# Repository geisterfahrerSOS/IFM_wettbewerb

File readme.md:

# THIS IS A TEST
Beware of software BUGS/ Feautures
Changes

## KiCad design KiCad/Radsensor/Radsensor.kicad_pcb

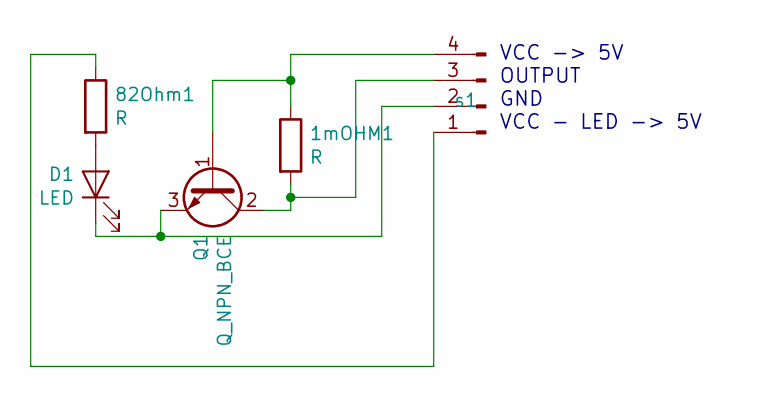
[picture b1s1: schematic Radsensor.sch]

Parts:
1mOHM1, 82Ohm1: R; R_Axial_DIN0204_L3.6mm_D1.6mm_P7.62mm_Horizontal
D1: LED; LED_D4.0mm
Q1: Q_NPN_BCE; TO-92_Inline_Wide
s1: PinHeader_1x04_P2.54mm_Horizontal

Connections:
unnamed: 1mOHM1.1, Q1.1 (B), s1.4
unnamed: 1mOHM1.2, Q1.2 (C), s1.3
unnamed: 82Ohm1.1, s1.1
unnamed: 82Ohm1.2, D1.2 (A)
unnamed: D1.1 (K), Q1.3 (E), s1.2

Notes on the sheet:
VCC -> 5V OUTPUT GND VCC - LED -> 5V

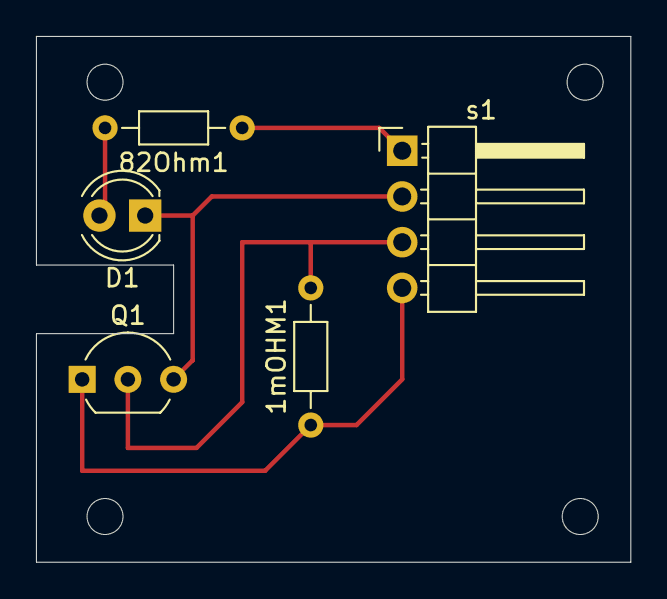
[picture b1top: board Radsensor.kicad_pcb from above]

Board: 2 copper layers, 33.0 x 29.2 mm, 5 parts (0 on the bottom side), 5 nets.

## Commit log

2020-02-14 library eingerichtet
2020-02-14 new commit
2020-02-14 added winkel Debug
2020-02-14 test
2020-02-14 deleted readme.md
2020-02-16 Test Webseite erstellt
2020-02-16 Test Fenster hinzugrfuegt
2020-02-16 Processing Project Start
2020-02-19 head style red
2020-02-19 made lol class
2020-02-19 changes blink to kompass in libraries
2020-02-19 created Kompass.cpp
2020-02-19 deleted blink .cpp
2020-02-19 renamed blink.h to Kompass.h
2020-02-19 more readme documentation
2020-02-19 replacing readme
2020-02-19 added debug funktion for testing
2020-02-19 added Kompass to libraries
2020-02-19 deleted Kompass in lib folder
2020-02-19 rehersal
2020-02-21 added display library
2020-02-21 cosmetic
2020-02-22 deleted test.html
2020-02-28 Projekte hinzugrfügt
2020-02-28 neuer Farbsensor - entwicklung
2020-02-29 Farbsensor TCS34725 als platformio projekt erstellt
2020-02-29 Farbsensor weitergemacht, Problem?: Enable-Reg
2020-03-02 Added LinienSensor to Entwicklung
2020-03-02 Neues main.cpp eingefügt leider kein hochladen über PlatformIO im Repository Aus vergangenen Bewgungen soll eine zukünftige bewegung besser durchgeführt werden Clean up FD: je nach zeit zwischen ände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
2020-03-02 added revised main.cpp FD: Roboter Steuerung ausarbeiten out of Bounds recovery einbinden von strecke anstatt von zeit leftShift rightShift toggle einarbeiten? (Soll die vergangenheit berücksuchtigt 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
2020-03-03 Added left right and stop; also added recovery mode for if the car is off the Line FD: Refine Motor controls add rotation function switch sides for attachment? add action rotation with compass remove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
2020-03-03 added Software Timer for main loop :-)
2020-03-04 added some Files to Webseite
2020-03-04 added radSensor Library Probleme mit object initialisierung
2020-03-04 some changes to library radsensor
2020-03-06 added radSensor main.cpp and library tweaks
2020-03-06 added Radsteuerung und radSensor Libraries Radsteuerung muss much drehung und drehung um fixen standpunkt coden
2020-03-07 added Radsteuerung_01 mit radDrehung funktion
2020-03-07 Änderungsvorschläge
2020-03-07 Änderungsvorschläge verbessert
2020-03-07 Aänderungsvorschläge verbessert2
2020-03-07 Buspirate - Test hinzugrfügt
2020-03-08 Vorgeschlagene Änderungen bei radSensor.h durchgeführt
2020-03-08 added updated Radsteuerung moved Webseite Folder to local HardDrive Moved Radsteuerung_01 to Entwicklung Nils muss noch Radsteuerung Library überprüfen
2020-03-08 small changes
2020-03-12 Testing the problems of the Sensor
2020-03-13 funkunierende Version des Farbsensors
2020-03-13 deleted Serial.println("MOIS"); in Kompass.cpp
2020-03-13 updated readme in Kompass.cpp
2020-03-13 added Radfahren to Radsteuerung
2020-03-15 neuste ENtwicklung am Motor mit Kompass Steuerung added
2020-03-15 variavlennamen geändert
2020-03-15 variablennamen geändert
2020-03-15 normale Farberkennung klappt, Zeit-Farberkennung aussteden, genaues Farbenlesen
2020-03-16 Farbmessung nach X-Zeit gefixed
2020-03-16 README hinzugegügt
2020-03-16 some simple driving changes to main
2020-03-17 Test mit dem Kompass
2020-03-18 Multiplexer Möglichkeit für Farbsensor eingebaut
2020-03-18 Test mit Multiplexer
2020-03-18 Multiplexermöglichkeit zu I2C-Libary hinzugeügt
2020-03-18 Ultraschall geändert
2020-03-18 Serialprint korrigiert
2020-03-20 drehen hinzugefügt funktioniert recht gut außer ein paar wahrscheinlich Hardware geschuldeten fehlern. Evtl. auch software beim übergang der beiden while schleifen TD: Die Radsonsoren fertig machen T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
2020-03-26 Farbsensor fertig gemacht
2020-03-27 Konstruktoren geändert
2020-03-28 SWtimer-Test
2020-03-28 SW-Timer klappt
2020-03-28 SWTimer
2020-03-28 added SoftwareTimer
2020-03-29 Drehen Funktion
2020-03-29 added updaets main.cpp to SoftwareTImer
2020-04-07 Farbe geändert
2020-04-07 farberkennung
2020-04-11 added softwaretimer11.04. to git
2020-04-15 KalmanFilter
2020-04-15 added softwaretumer new
2020-06-17 LinienSensor - swTimer
2020-08-05 Update swTimer / Radsensor
2020-08-05 Radsensor-Platine
2020-08-06 Update der Platine
